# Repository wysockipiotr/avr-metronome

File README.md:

<h1 align="center">AVR Metronome</h1>
<h5 align="center">Metronome with speaker and remote vibration module</h5>

#### Modules
<table>
<tr>
  <td style="text-align: center">
    
  </td>
  <td style="text-align: center">
    
  </td>
</tr>
</table>

#### Built with
- ATmega 168A-PU
- Qduino Mini
- MCP4161
- TPA2005D1
- HM-10 BLE

#### Features
- [x] Sound mode with volume control
- [x] Rotary encoder (with push button) user interface
- [x] BPM and basic signatures control
- [x] Tap tempo (button)
- [x] PWM LCD backlight (dimming after a period of inactivity)
- [x] Storing metronome settings in the internal EEPROM
- [x] Custom character display
- [x] Remote vibration module (BLE)
- [x] Default idle state for remote module, receiving disable signal
- [x] MicroUSB charging
- [x] Adjustable sound pitch

#### Project structure
```c
+-- 
   +-- README.md
   +-- .gitignore
   +-- doc
      +-- eagle
         +-- main
         +-- remote
   +-- metronome          // ATmega metronome main module directory
      +-- Makefile        // compiler and programmer config
      +-- main.c          // entry point
      +-- setup.h         // device main settings
      +-- util.h          // helper macros
      +-- global.h        // extern declarations
      +-- lcd.h           // LCD 2x16 interfacing in 4-bit mode
      +-- lcd.c
      +-- eeprom.h
      +-- eeprom.c
      +-- metronome.h     // core logic of the metronome, ISR handlers
      +-- metronome.c
      +-- usart.h         // serial communication with HM-10 BLE module
      +-- usart.c
      +-- mcp41xx.h       // MCP4161 Digital potentiometer SPI interfacing
      +-- mcp41xx.c
   +-- remote_module      // Qduino (Arduino) remote vibrating module sketch directory
      +-- README.md
      +-- remote_module.ino
```

#### Setup
##### Prerequisites
- make
- avrdude
- avr-gcc
##### Makefile
Override parameters in Makefile to suit your hardware configuration. Here, Arduino Uno is used as an in-system programmer.
```diff
- MCU = atmega168
+ MCU = <your_unit>

- PROGRAMMER_TYPE = avrisp
- PROGRAMMER_ARGS = -b 19200 -P COM4
+ PROGRAMMER_TYPE = <your_programmer_type>
+ PROGRAMMER_ARGS = -b <baud_rate> -P <device_name>
```
##### Deployment
Use `make flash` to compile and save program in flash memory (using `avrdude`). Use `make size` to find out about the size of the program.

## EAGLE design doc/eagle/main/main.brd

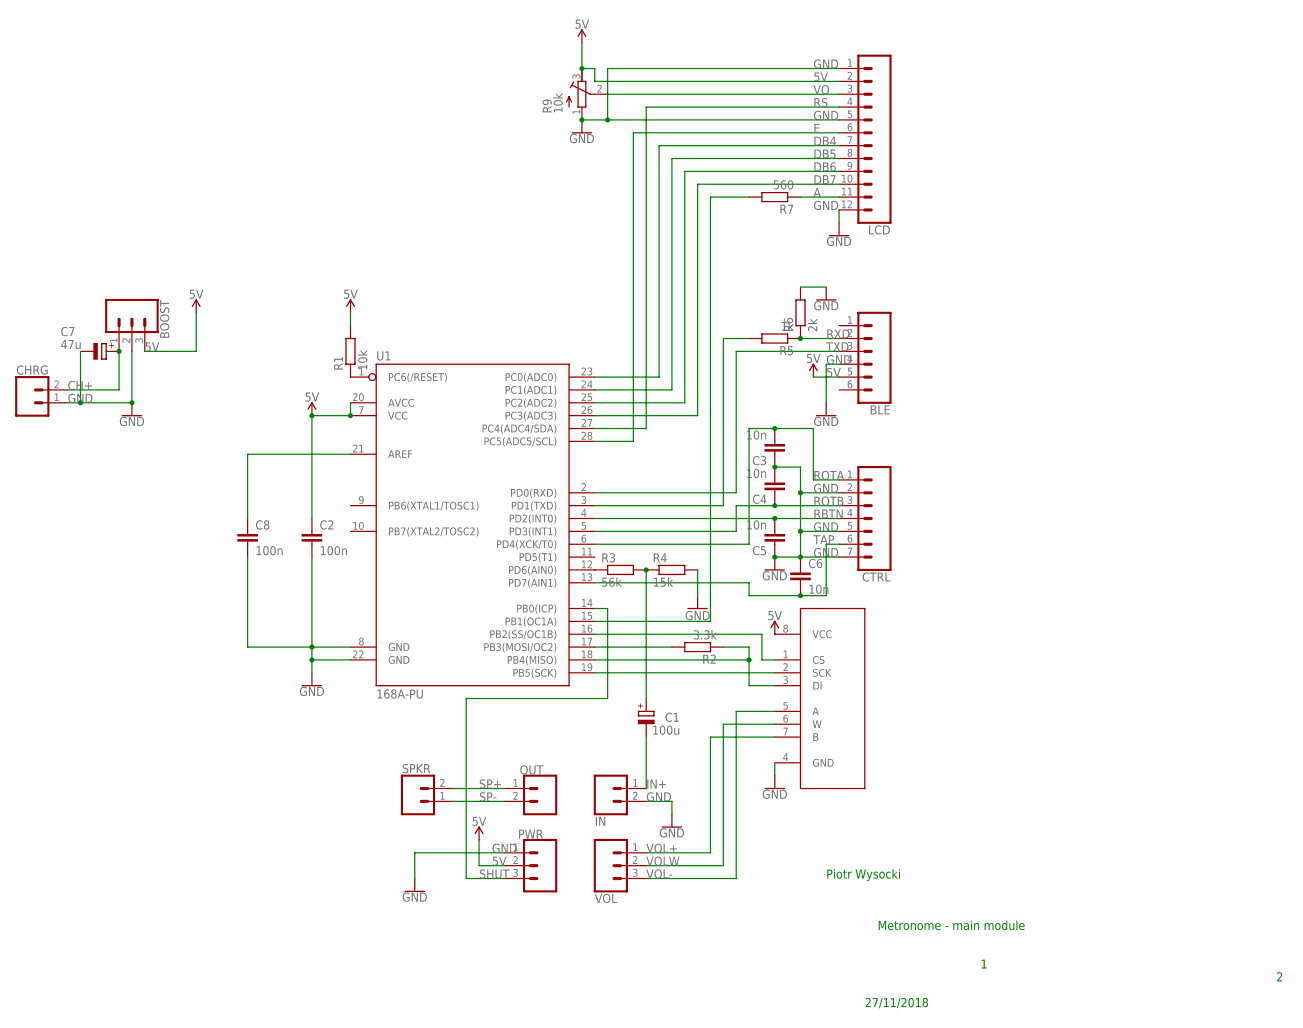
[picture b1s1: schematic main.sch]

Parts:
BLE: CONN_06SILK_FEMALE_PTH; 1X06
BOOST: CONN_03; 1X03
C1: 100u; E3,5-8
C2, C8: 100n; C025-024X044
C3, C4, C5, C6: 10n; C025-024X044
C7: 47u; E2,5-7
CHRG: CONN_02; 1X02
CTRL: CONN_07; 1X07
IN: CONN_02; 1X02
LCD: CONN_12; 1X12
MCP4161: MCP41XXX; DIP08
OUT: CONN_02; 1X02
PWR: CONN_03; 1X03
R1: 10k; 0204/7
R2: 3.3k; 0204/7
R3: 56k; 0204/7
R4: 15k; 0204/7
R5: 1k; 0204/7
R6: 2k; 0204/7
R7: 560; 0204/7
R9: 10k; RTRIM3296W
SPKR: CONN_02; 1X02
U1: 168A-PU; DIP28
VOL: CONN_03; 1X03

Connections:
5V: BLE.5, BOOST.3, C2.1, LCD.2, MCP4161.8 (VCC), PWR.2, R1.2, R9.3 (E), U1.7 (VCC), U1.20 (AVCC)
A: LCD.11, R7.1
CH+: BOOST.1, C7.+, CHRG.2
DB4: LCD.7, U1.23 (PC0(ADC0))
DB5: LCD.8, U1.24 (PC1(ADC1))
DB6: LCD.9, U1.25 (PC2(ADC2))
DB7: LCD.10, U1.26 (PC3(ADC3))
E: LCD.6, U1.28 (PC5(ADC5/SCL))
GND: BLE.4, BOOST.2, C2.2, C3.1, C4.2, C5.1, C6.1, C7.-, C8.2, CHRG.1, CTRL.2, CTRL.5, CTRL.7, IN.2, LCD.1, LCD.5, LCD.12, MCP4161.4 (GND), PWR.1, R4.2, R6.2, R9.1 (A), U1.8 (GND), U1.22 (GND)
IN+: C1.-, IN.1
unnamed: MCP4161.2 (SCK), U1.19 (PB5(SCK))
unnamed: MCP4161.1 (CS), U1.16 (PB2(SS/OC1B))
unnamed: R1.1, U1.1 (PC6(/RESET))
unnamed: R2.2, U1.17 (PB3(MOSI/OC2))
unnamed: MCP4161.3 (DI), R2.1, U1.18 (PB4(MISO))
unnamed: C8.1, U1.21 (AREF)
unnamed: R3.1, U1.12 (PD6(AIN0))
unnamed: C1.+, R3.2, R4.1
unnamed: R5.2, U1.3 (PD1(TXD))
unnamed: R7.2, U1.15 (PB1(OC1A))
RBTN: C5.2, CTRL.4, U1.4 (PD2(INT0))
ROTA: C3.2, CTRL.1, U1.6 (PD4(XCK/T0))
ROTB: C4.1, CTRL.3, U1.5 (PD3(INT1))
RS: LCD.4, U1.27 (PC4(ADC4/SDA))
RXD: BLE.2, R5.1, R6.1
SHUT: PWR.3, U1.14 (PB0(ICP))
SP+: OUT.1, SPKR.2
SP-: OUT.2, SPKR.1
TAP: C6.2, CTRL.6, U1.13 (PD7(AIN1))
TXD: BLE.3, U1.2 (PD0(RXD))
VO: LCD.3, R9.2 (S)
VOL+: MCP4161.7 (B), VOL.1
VOL-: MCP4161.5 (A), VOL.3
VOLW: MCP4161.6 (W), VOL.2

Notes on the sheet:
Metronome - main module
Piotr Wysocki
27/11/2018

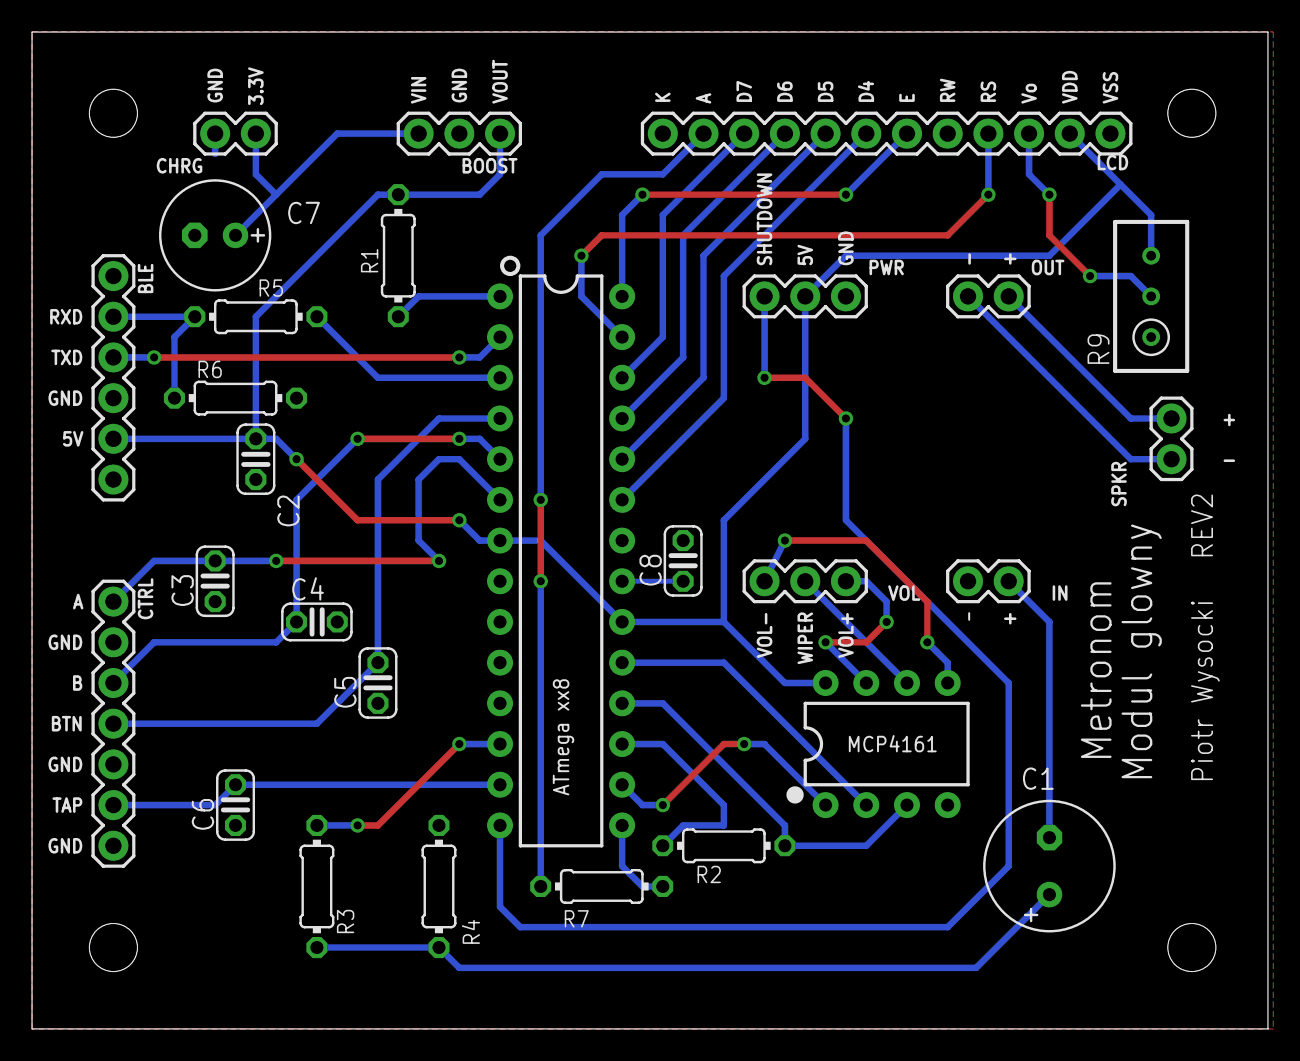
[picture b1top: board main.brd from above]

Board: 2 copper layers, 77.1 x 62.2 mm, 28 parts (0 on the bottom side), 34 nets.

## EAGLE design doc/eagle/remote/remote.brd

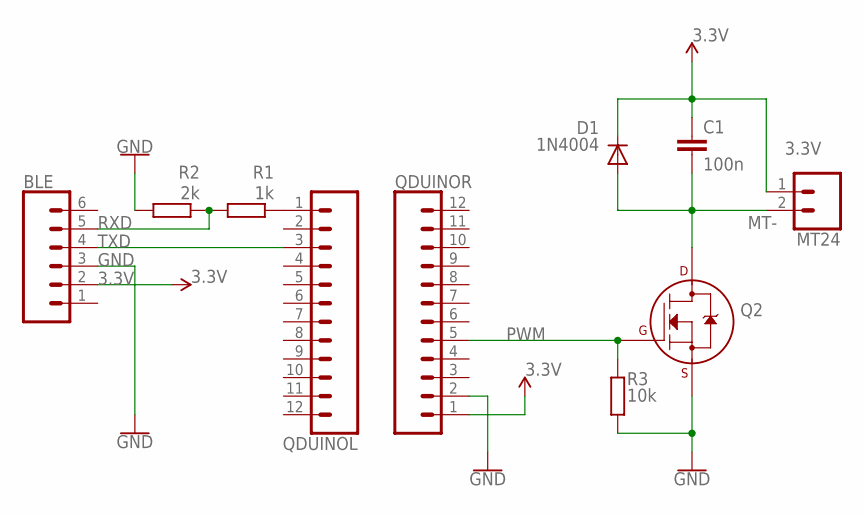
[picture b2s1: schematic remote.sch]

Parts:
BLE: CONN_06SILK_FEMALE_PTH; 1X06
C1: 100n; C025-024X044
D1: 1N4004; DO41-10
MT24: CONN_02; 1X02
Q2: 2N7000_TO92; TO-92
QDUINOL: CONN_12; 1X12
QDUINOR: CONN_12; 1X12
R1: 1k; 0204/7
R2: 2k; 0204/7
R3: 10k; 0204/7

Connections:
3.3V: BLE.2, C1.1, D1.C, MT24.1, QDUINOR.1
GND: BLE.3, Q2.1 (S), QDUINOR.2, R2.2, R3.2
MT-: C1.2, D1.A, MT24.2, Q2.3 (D)
unnamed: QDUINOL.1, R1.1
PWM: Q2.2 (G), QDUINOR.5, R3.1
RXD: BLE.5, R1.2, R2.1
TXD: BLE.4, QDUINOL.3

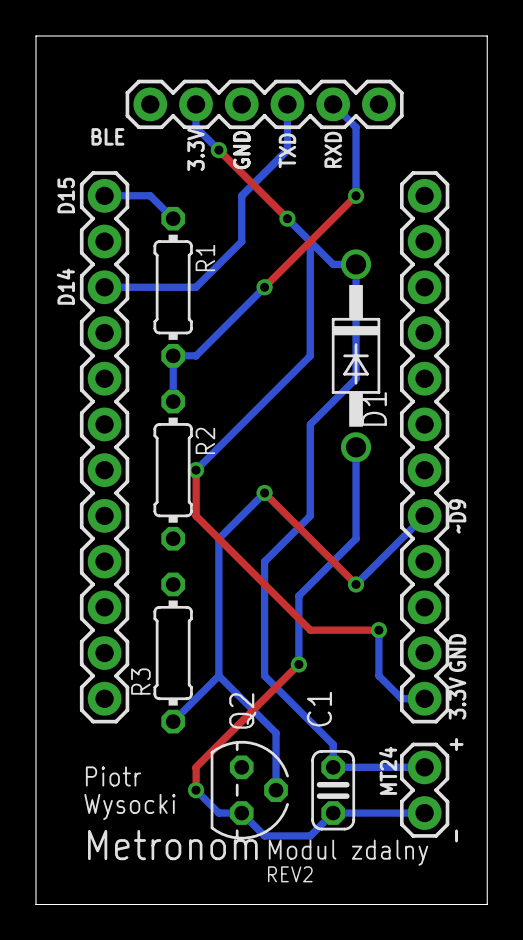
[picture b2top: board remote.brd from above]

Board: 2 copper layers, 25.1 x 48.2 mm, 10 parts (0 on the bottom side), 7 nets.

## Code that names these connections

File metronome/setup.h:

#ifndef __setup_h__
#define __setup_h__

#ifdef F_CPU
    #if F_CPU != 8000000
        #undef F_CPU
        #define F_CPU 8000000
    #endif
#endif

#ifndef BAUD
    #define BAUD 9600
#endif

#include <avr/io.h>
#include "lcd.h"

#define LCD_DIR                     DDRC  
#define LCD_DATA_DIR                DDRC
#define LCD_CMD_DIR                 DDRC
#define LCD_DATA_PORT               DDRC 
#define LCD_CMD_PORT                PORTC
#define LCD_PORT                    PORTC 
#define RS                          PC4 
#define EN                          PC5
#define LCD_D4                      PC0 
#define LCD_D5                      PC1   
#define LCD_D6                      PC2   
#define LCD_D7                      PC3   

#define ROTARY_PORT                 PORTD
#define ROTARY_BTN                  PD2
#define ROTARY_PIN                  PIND
#define ROTARY_DIR                  DDRD
#define ROTARY_A                    PD3
#define ROTARY_B                    PD4

#define SPEAKER_DIR                 DDRD
#define SPEAKER_PORT                PORTD
#define SPEAKER                     PD6
#define SPEAKER_PIN                 PIND

#define TAP_DIR                     DDRD
#define TAP_PORT                    PORTD
#define TAP_PIN                     PIND
#define TAP_BTN                     PD7

#define SHUTDOWN_DIR                DDRB
#define SHUTDOWN_PORT               PORTB
#define SHUTDOWN_PIN                PINB
#define SHUTDOWN                    PB0

#define BACKLIGHT_DIR               DDRB
#define BACKLIGHT_PORT              PORTB
#define BACKLIGHT_PIN               PINB
#define BACKLIGHT                   PB1

// SPI
#define SPI_POT_SS                  PB2
#define SPI_POT_SS_PORT             PORTB
#define SPI_POT_SS_PIN              PINB
#define SPI_POT_SS_DDR              DDRB

#define SPI_MOSI                    PB3
#define SPI_MOSI_PORT               PORTB
#define SPI_MOSI_PIN                PINB
#define SPI_MOSI_DDR                DDRB

#define SPI_MISO                    PB4
#define SPI_MISO_PORT               PORTB
#define SPI_MISO_PIN                PINB
#define SPI_MISO_DDR                DDRB

#define SPI_SCK                     PB5
#define SPI_SCK_PORT                PORTB
#define SPI_SCK_PIN                 PINB
#define SPI_SCK_DDR                 DDRB

#define TAP_TIMER_INITIAL_OFFSET    0x83
#define MIN_TAP_INTERVAL            150u
#define MAX_TAP_INTERVAL            2000u

#define BACKLIGHT_DURATION          20000u  // 20s
#define DEFAULT_BRIGHTNESS          120u

#define MIN_BPM                     30u
#define MAX_BPM                     400u
#define MIN_VOLUME                  0u
#define MAX_VOLUME                  100u
#define VOLUME_STEP                 5u
#define DEFAULT_BPM                 140u
#define DEFAULT_VOL                 5u
#define DEFAULT_SIGNATURE           4u
#define MIN_SIGNATURE               1u 
#define MAX_SIGNATURE               16u
#define G                           33u
#define CIS                         47u
#define TAP_NOTE                    120u
#define TAP_BEEP_DURATION           100u

#define BPM_CURSOR_POS              0u
#define SIG_CURSOR_POS              1u 
#define VOL_CURSOR_POS              2u
#define MODE_CURSOR_POS             3u
#define PITCH_CURSOR_POS            4u

#define PARAM_EDIT_SYMBOL           LCD_ARROWS_CHAR
#define PARAM_SELECT_SYMBOL         LCD_FAT_ARROW_CHAR

#define SOUND_LABEL                 "SOUND"
#define VIBRT_LABEL                 "VIBRT"

#define SOUND_MODE                  0u 
#define VIBRT_MODE                  1u
#define DEFAULT_MODE                SOUND_MODE

#define NUMBER_OF_MODES             2
// #define NUMBER_OF_SIGNATURES        4

#define EEPROM_STORE_ADR            0
#define EEPROM_STORE_BPM            ((uint16_t*)EEPROM_STORE_ADR)
#define EEPROM_STORE_VOL            ((uint8_t*)EEPROM_STORE_ADR + 2)
#define EEPROM_STORE_SIG            ((uint8_t*)EEPROM_STORE_ADR + 3)
#define EEPROM_STORE_MODE           ((uint8_t*)EEPROM_STORE_ADR + 4)
#define EEPROM_STORE_PITCH          ((uint8_t*)EEPROM_STORE_ADR + 5)

// sound scale
#define D2                          89
#define Dx2                         84
#define E2                          79
#define F2                          75
#define Fx2                         71
#define G2                          67
#define Gx2                         63
#define A2                          59
#define Ax2                         56
#define B2                          53
#define C3                          50
#define Cx3                         47
#define D3                          44
#define Dx3                         42
#define E3                          40
#define F3                          37
#define Fx3                         35
#define G3                          33

#define DEFAULT_PITCH_INDEX         11u
#define MAX_PITCH_INDEX             11u
#define MIN_PITCH_INDEX             0u
#define ACCENT_PITCH_OFFSET         6u

#endif //__setup_h__

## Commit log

2018-11-20 Init, utilities, setup, 2x16 lcd interfacing
2018-11-20 Interrupts for rotary encoder and buttons, timer0 based sound generator, timer1 based tap tempo, basic metronome
2018-11-21 Refactored functions
2018-11-21 Toggleable parameter value adjustment mode. Comments for global variables.
2018-11-21 Division into separate directories.
2018-11-21 Added MCP41xx chip interfacing through SPI
2018-11-22 ISRs refactored, globals header
2018-11-22 Arduino vibrating module sketch origins
2018-11-22 README Project structure
2018-11-24 Basic USART communication
2018-11-27 PWM LCD dimmable backlight, metronome mode switching origins
2018-11-27 Eagle main module schematic (version with connectors)
2018-11-27 Updated README.md: setup, schematic
2018-11-30 Vibration motor output"
2018-12-01 Custom character display (bytes loaded from program memory)
2018-12-01 UI improvements, unlocking amp for tap tempo beeps
2018-12-01 Fixed Vibrt mode params update on edit mode exit
2018-12-09 Eagle files, eeprom empty *.h and *.c
2018-12-09 Schematic images added
2018-12-09 View schematics in README file
2018-12-09 Global variables moved from main.c to global.c
2019-01-05 Storing metronome params in EEPROM after user inactivity, Eagle files + PDF exports
2019-01-05 Qduino sketch refactor, receiving remote-disable signal
2019-01-20 Debounced tap tempo beeps of constant duration
2019-01-20 Pitch tuning, second menu page
2019-01-20 Cursor bug fix, vibrations disable signal on rotary button pushed
2019-01-20 Remote module signature format change, more frequent settings update polling
2019-01-22 README update

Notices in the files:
parts and their libraries:
SparkFun-Connectors: Licensing: Creative Commons ShareAlike 4.0 International - https://creativecommons.org/licenses/by-sa/4.0
